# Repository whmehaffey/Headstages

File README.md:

# Headstages

Parts List/Assembly Instructions here:
https://drive.google.com/drive/folders/19IeQBwkrlpiADKMYrT-vz9yy6rZNcAjY?usp=sharing

The video is old and uses an old PCB design (with a bad connection), but the principles are the same. Also, it uses a giant heat gun, but it's a lot easier with a reflow workstation like this one from Adafruit: (https://www.adafruit.com/product/1869)

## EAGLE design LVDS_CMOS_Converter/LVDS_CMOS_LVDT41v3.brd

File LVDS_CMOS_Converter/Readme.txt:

Uses SN65LVDT41QPWREP to converts CMOS to LVDS to interface w/ Intan Evel board. Was originally built to interface w/ Dragonfly commutators (DB9 or DB15 version).

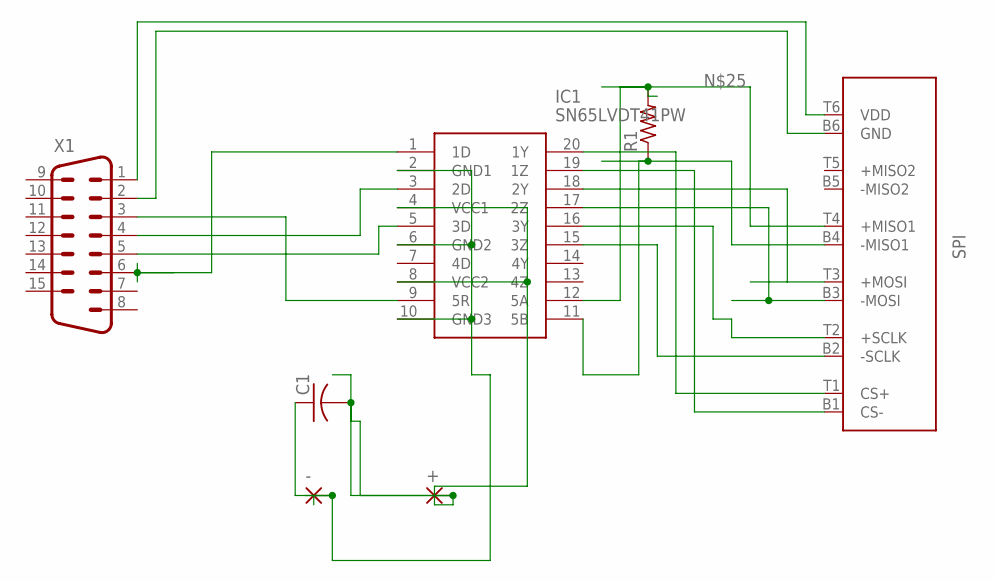
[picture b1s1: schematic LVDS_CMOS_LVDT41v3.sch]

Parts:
+: 3,17/1,3
-: 3,17/1,3
C1: C-USC0805; C0805
IC1: SN65LVDT41PW; SOP65P640X120-20N
R1: R-US_R0603; R0603
SPI: SPI; OMNETICS_PZN-12-AA-UPDATED
X1: M15H

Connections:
BRD_GND: -.1, C1.1, IC1.2 (GND1), IC1.6 (GND2), IC1.10 (GND3)
unnamed: SPI.T6 (VDD), X1.1
unnamed: SPI.B6 (GND), X1.2
unnamed: IC1.1 (1D), X1.6
unnamed: IC1.9 (5R), X1.3
unnamed: IC1.3 (2D), X1.4
unnamed: IC1.5 (3D), X1.5
unnamed: IC1.16 (3Y), SPI.T2 (+SCLK)
unnamed: IC1.15 (3Z), SPI.B2 (-SCLK)
unnamed: IC1.18 (2Y), SPI.T3 (+MOSI)
unnamed: IC1.17 (2Z), SPI.B3 (-MOSI)
unnamed: IC1.12 (5A), R1.2, SPI.T4 (+MISO1)
unnamed: IC1.11 (5B), R1.1, SPI.B4 (-MISO1)
unnamed: IC1.19 (1Z), SPI.B1 (CS-)
unnamed: IC1.20 (1Y), SPI.T1 (CS+)
VDD-3.3V: +.1, C1.2, IC1.4 (VCC1), IC1.8 (VCC2)

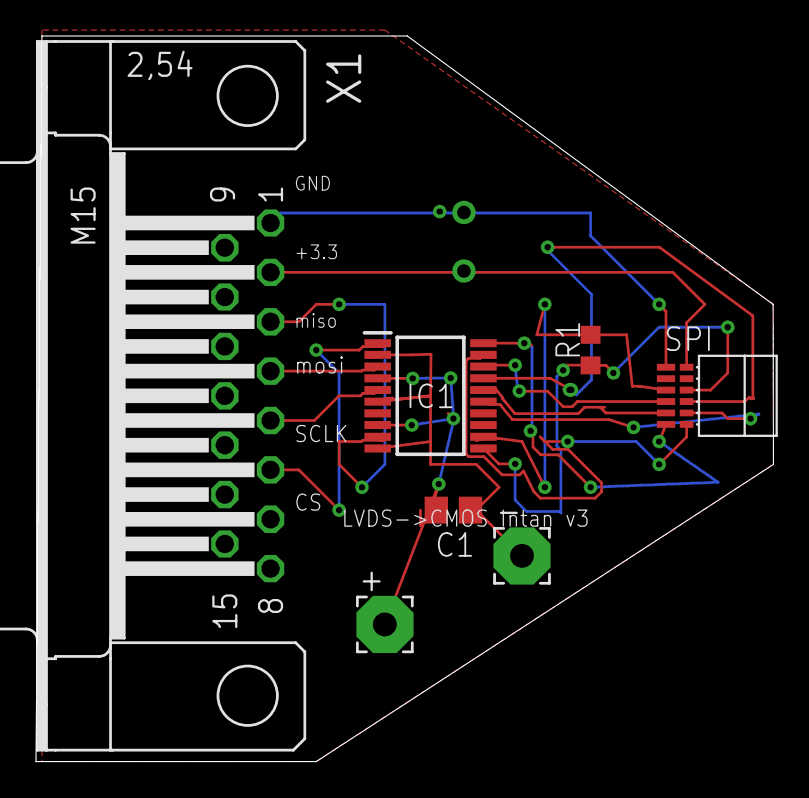
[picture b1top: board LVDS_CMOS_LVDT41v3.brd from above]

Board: 2 copper layers, 41.0 x 40.3 mm, 7 parts (0 on the bottom side), 16 nets.

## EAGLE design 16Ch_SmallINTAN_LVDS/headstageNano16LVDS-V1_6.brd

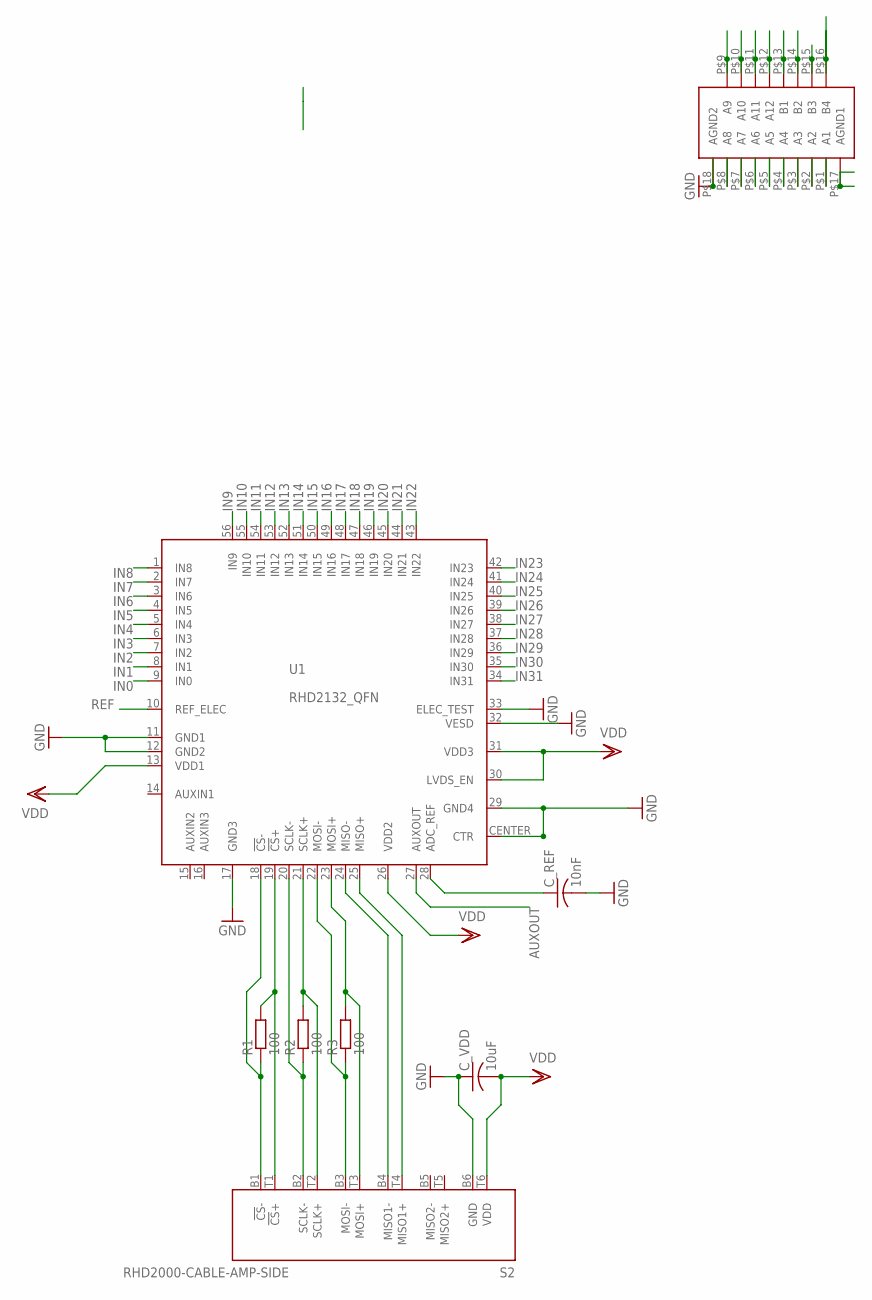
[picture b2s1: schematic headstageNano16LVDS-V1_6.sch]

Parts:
C_REF: 10nF; C0402K
C_VDD: 10uF; C0402K
R1, R2, R3: 100; R0402
S2: RHD2000-CABLE-AMP-SIDE; OMNETICS_PZN-12-AA
U1: RHD2132_QFN; QFN56_8_X_8_LARGE
U$1: OMNETICS_FE18

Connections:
ADC_REF: C_REF.1, U1.28 (ADC_REF)
AGND1: U$1.P$17 (AGND1)
AUXOUT: U1.27 (AUXOUT)
CS+: R1.2, S2.T1 (!CS!+), U1.19 (!CS!+)
CS-: R1.1, S2.B1 (!CS!-), U1.18 (!CS!-)
GND: C_REF.2, C_VDD.1, S2.B6 (GND), U1.11 (GND1), U1.12 (GND2), U1.17 (GND3), U1.29 (GND4), U1.32 (VESD), U1.33 (ELEC_TEST), U1.CENTER (CTR), U$1.P$18 (AGND2)
IN0: U1.9 (IN0)
IN1: U1.8 (IN1)
IN2: U1.7 (IN2)
IN3: U1.6 (IN3)
IN4: U1.5 (IN4)
IN5: U1.4 (IN5)
IN6: U1.3 (IN6)
IN7: U1.2 (IN7)
IN8: U1.1 (IN8)
IN9: U1.56 (IN9)
IN10: U1.55 (IN10)
IN11: U1.54 (IN11)
IN12: U1.53 (IN12)
IN13: U1.52 (IN13)
IN14: U1.51 (IN14)
IN15: U1.50 (IN15)
IN16: U1.49 (IN16)
IN17: U1.48 (IN17)
IN18: U1.47 (IN18)
IN19: U1.46 (IN19)
IN20: U1.45 (IN20)
IN21: U1.44 (IN21)
IN22: U1.43 (IN22)
IN23: U1.42 (IN23)
IN24: U1.41 (IN24)
IN25: U1.40 (IN25)
IN26: U1.39 (IN26)
IN27: U1.38 (IN27)
IN28: U1.37 (IN28)
IN29: U1.36 (IN29)
IN30: U1.35 (IN30)
IN31: U1.34 (IN31)
IN32: U$1.P$14 (B2)
IN34: U$1.P$16 (B4)
IN35: U$1.P$2 (A2)
IN36: U$1.P$15 (B3)
IN37: U$1.P$3 (A3)
IN38: U$1.P$12 (A12)
IN39: U$1.P$13 (B1)
IN40: U$1.P$5 (A5)
IN41: U$1.P$4 (A4)
IN42: U$1.P$6 (A6)
IN43: U$1.P$7 (A7)
IN44: U$1.P$10 (A10)
IN45: U$1.P$8 (A8)
IN46: U$1.P$9 (A9)
IN47: U$1.P$1 (A1)
IN48: U$1.P$11 (A11)
MISO1+: S2.T4 (MISO1+), U1.25 (MISO+)
MISO1-: S2.B4 (MISO1-), U1.24 (MISO-)
MOSI+: R3.2, S2.T3 (MOSI+), U1.23 (MOSI+)
MOSI-: R3.1, S2.B3 (MOSI-), U1.22 (MOSI-)
REF: U1.10 (REF_ELEC)
SCLK+: R2.2, S2.T2 (SCLK+), U1.21 (SCLK+)
SCLK-: R2.1, S2.B2 (SCLK-), U1.20 (SCLK-)
VDD: C_VDD.2, S2.T6 (VDD), U1.13 (VDD1), U1.26 (VDD2), U1.30 (LVDS_EN), U1.31 (VDD3)

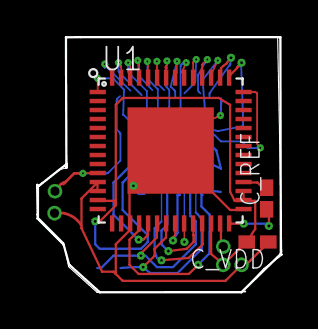
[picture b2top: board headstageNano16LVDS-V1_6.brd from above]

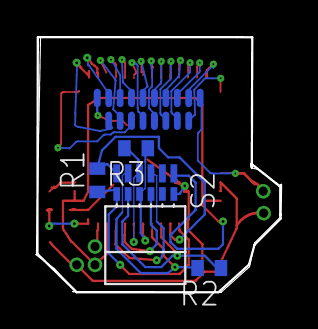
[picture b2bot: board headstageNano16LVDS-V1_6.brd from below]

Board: 2 copper layers, 13.6 x 14.2 mm, 8 parts (4 on the bottom side), 11 nets.

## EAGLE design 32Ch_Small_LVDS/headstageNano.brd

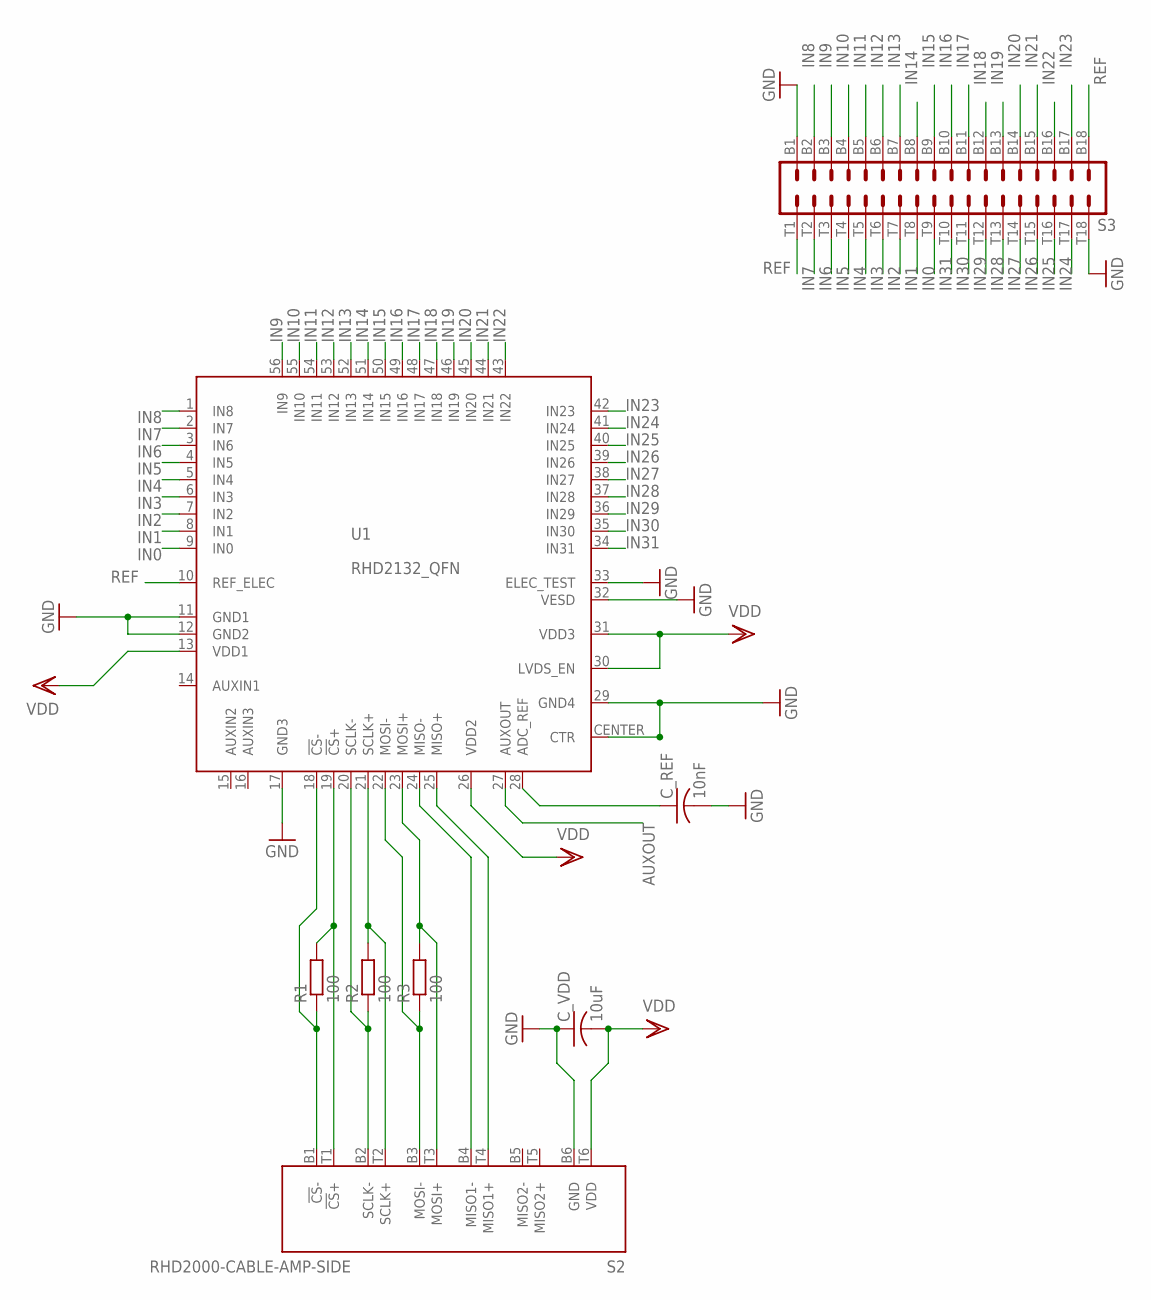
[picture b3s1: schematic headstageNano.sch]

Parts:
C_REF: 10nF; C0402K
C_VDD: 10uF; C0402K
R1, R2, R3: 100; R0402
S2: RHD2000-CABLE-AMP-SIDE; OMNETICS_PZN-12-AA
S3: OMNETICS_A79025
U1: RHD2132_QFN; QFN56_8_X_8_LARGE

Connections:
ADC_REF: C_REF.1, U1.28 (ADC_REF)
AUXOUT: U1.27 (AUXOUT)
CS+: R1.2, S2.T1 (!CS!+), U1.19 (!CS!+)
CS-: R1.1, S2.B1 (!CS!-), U1.18 (!CS!-)
GND: C_REF.2, C_VDD.1, S2.B6 (GND), S3.B1, S3.T18, U1.11 (GND1), U1.12 (GND2), U1.17 (GND3), U1.29 (GND4), U1.32 (VESD), U1.33 (ELEC_TEST), U1.CENTER (CTR)
IN0: S3.T9, U1.9 (IN0)
IN1: S3.T8, U1.8 (IN1)
IN2: S3.T7, U1.7 (IN2)
IN3: S3.T6, U1.6 (IN3)
IN4: S3.T5, U1.5 (IN4)
IN5: S3.T4, U1.4 (IN5)
IN6: S3.T3, U1.3 (IN6)
IN7: S3.T2, U1.2 (IN7)
IN8: S3.B2, U1.1 (IN8)
IN9: S3.B3, U1.56 (IN9)
IN10: S3.B4, U1.55 (IN10)
IN11: S3.B5, U1.54 (IN11)
IN12: S3.B6, U1.53 (IN12)
IN13: S3.B7, U1.52 (IN13)
IN14: S3.B8, U1.51 (IN14)
IN15: S3.B9, U1.50 (IN15)
IN16: S3.B10, U1.49 (IN16)
IN17: S3.B11, U1.48 (IN17)
IN18: S3.B12, U1.47 (IN18)
IN19: S3.B13, U1.46 (IN19)
IN20: S3.B14, U1.45 (IN20)
IN21: S3.B15, U1.44 (IN21)
IN22: S3.B16, U1.43 (IN22)
IN23: S3.B17, U1.42 (IN23)
IN24: S3.T17, U1.41 (IN24)
IN25: S3.T16, U1.40 (IN25)
IN26: S3.T15, U1.39 (IN26)
IN27: S3.T14, U1.38 (IN27)
IN28: S3.T13, U1.37 (IN28)
IN29: S3.T12, U1.36 (IN29)
IN30: S3.T11, U1.35 (IN30)
IN31: S3.T10, U1.34 (IN31)
MISO1+: S2.T4 (MISO1+), U1.25 (MISO+)
MISO1-: S2.B4 (MISO1-), U1.24 (MISO-)
MOSI+: R3.2, S2.T3 (MOSI+), U1.23 (MOSI+)
MOSI-: R3.1, S2.B3 (MOSI-), U1.22 (MOSI-)
REF: S3.B18, S3.T1, U1.10 (REF_ELEC)
SCLK+: R2.2, S2.T2 (SCLK+), U1.21 (SCLK+)
SCLK-: R2.1, S2.B2 (SCLK-), U1.20 (SCLK-)
VDD: C_VDD.2, S2.T6 (VDD), U1.13 (VDD1), U1.26 (VDD2), U1.30 (LVDS_EN), U1.31 (VDD3)

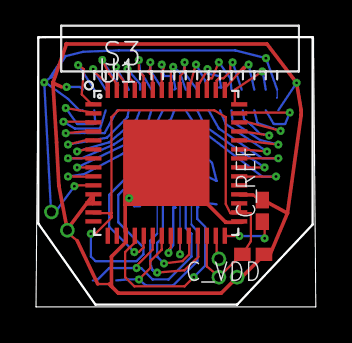
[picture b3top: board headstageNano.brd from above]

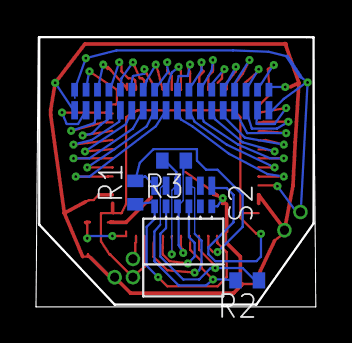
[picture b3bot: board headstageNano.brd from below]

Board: 2 copper layers, 15.5 x 15.0 mm, 8 parts (4 on the bottom side), 44 nets.

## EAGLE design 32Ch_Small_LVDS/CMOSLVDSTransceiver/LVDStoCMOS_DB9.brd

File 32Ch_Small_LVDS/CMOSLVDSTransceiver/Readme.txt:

Uses SN65LVDT41QPWREP to go from CMOS to LVDS and back, interfaces between a Dragonfly commutator (DB9 for 6Ch, DB15 for 10).

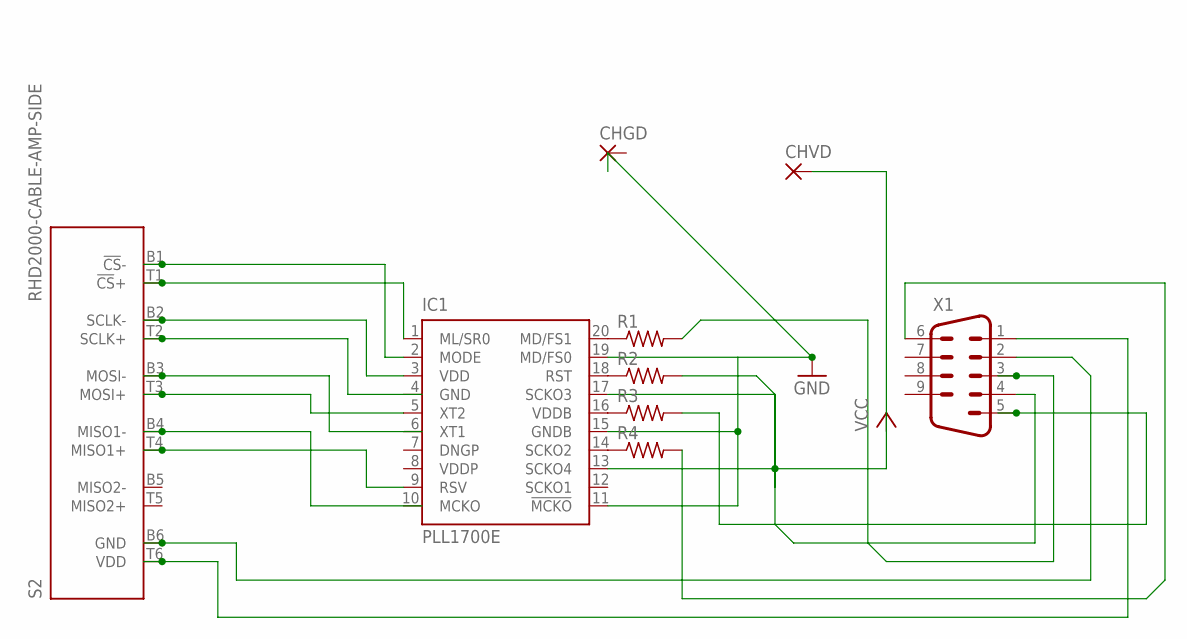
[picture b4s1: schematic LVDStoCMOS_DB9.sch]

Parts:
CHGD: 1,6/0,8
CHVD: 1,6/0,8
IC1: PLL1700E; SSOP20
R1, R2, R3, R4: R-US_R0402; R0402
S2: RHD2000-CABLE-AMP-SIDE; OMNETICS_PZN-12-AA
X1: M09H

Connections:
DNGP: IC1.7 (DNGP)
GND: IC1.4 (GND), IC1.11 (!MCKO), IC1.15 (GNDB), IC1.19 (MD/FS0)
unnamed: IC1.20 (MD/FS1), R1.1
unnamed: IC1.18 (RST), R2.1
unnamed: IC1.16 (VDDB), R3.1
unnamed: IC1.14 (SCKO2), R4.1
unnamed: IC1.2 (MODE), S2.B1 (!CS!-)
unnamed: CHVD.1, IC1.13 (SCKO4), IC1.17 (SCKO3)
unnamed: IC1.1 (ML/SR0), S2.T1 (!CS!+)
unnamed: IC1.3 (VDD), S2.B2 (SCLK-)
unnamed: IC1.5 (XT2), S2.T3 (MOSI+)
unnamed: IC1.9 (RSV), S2.T4 (MISO1+)
unnamed: R1.2, X1.3
unnamed: S2.B6 (GND), X1.2
unnamed: S2.T6 (VDD), X1.1
unnamed: R2.2, X1.4
unnamed: R3.2, X1.5
unnamed: R4.2, X1.6
VDDP: IC1.8 (VDDP)

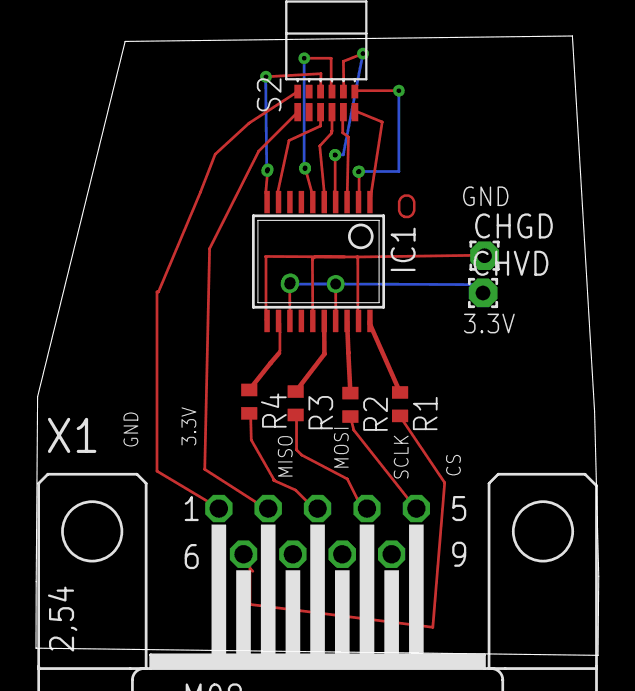
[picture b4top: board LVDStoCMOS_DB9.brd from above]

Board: 2 copper layers, 31.3 x 34.4 mm, 9 parts (0 on the bottom side), 17 nets.

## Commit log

2018-10-24 Initial commit
    Set of headtages and converters for light-weight versions of the Intan headstages, based on the INTAN 2132 chip. 16 and 32Ch LVDS versions, and 16Ch CMOS version, requiring a converter to interface w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
